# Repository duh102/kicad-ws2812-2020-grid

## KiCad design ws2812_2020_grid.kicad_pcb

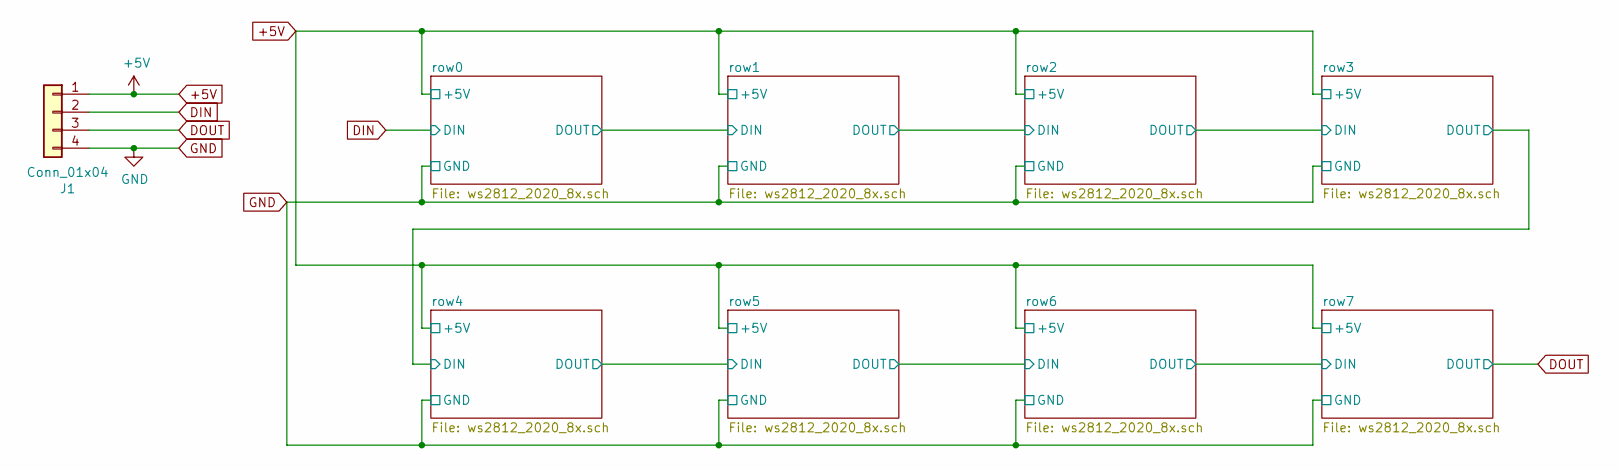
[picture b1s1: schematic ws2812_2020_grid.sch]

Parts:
J1: Conn_01x04; PinHeader_1x04_P2.54mm_Vertical

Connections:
+5V: J1.1; also elsewhere on the board
DIN: J1.2; also elsewhere on the board
DOUT: J1.3; also elsewhere on the board
GND: J1.4; also elsewhere on the board

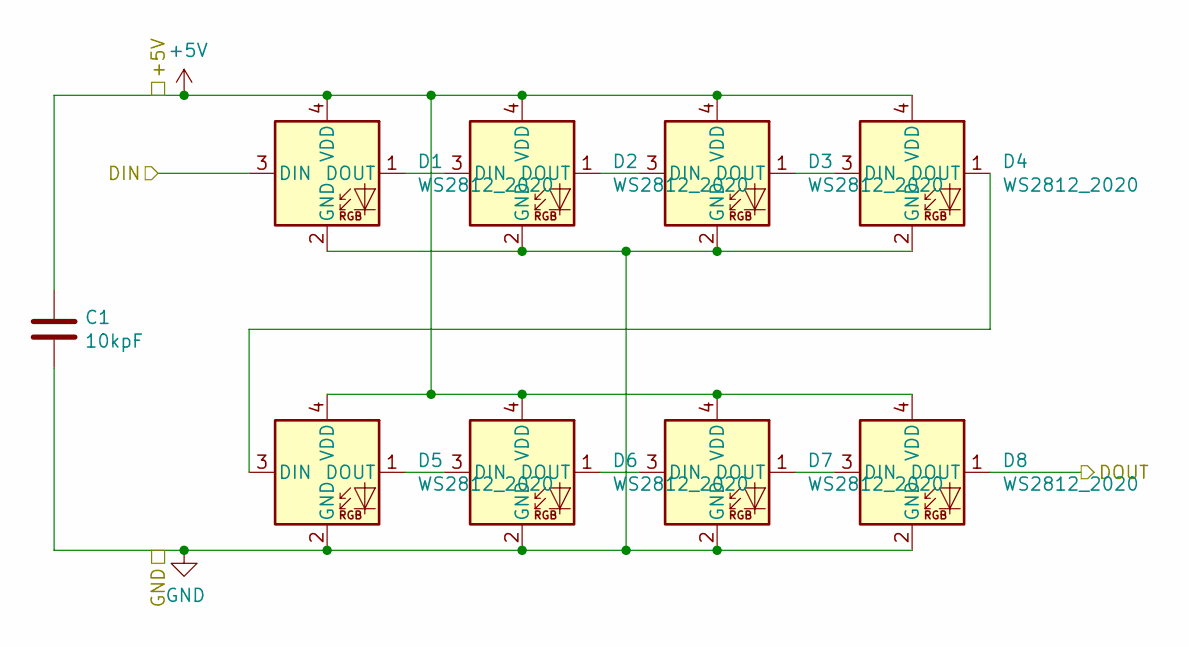
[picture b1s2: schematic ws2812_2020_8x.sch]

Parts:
C1: 10kpF; C_0805_2012Metric
D1, D2, D3, D4, D5, D6, D7, D8: WS2812_2020; LED_WS2812_2020_2.0x2.0mm

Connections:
+5V: C1.1, D1.4 (VDD), D2.4 (VDD), D3.4 (VDD), D4.4 (VDD), D5.4 (VDD), D6.4 (VDD), D7.4 (VDD), D8.4 (VDD); also elsewhere on the board
/row1/DIN: D8.1 (DOUT); also elsewhere on the board
DIN: D1.3 (DIN); also elsewhere on the board
GND: C1.2, D1.2 (GND), D2.2 (GND), D3.2 (GND), D4.2 (GND), D5.2 (GND), D6.2 (GND), D7.2 (GND), D8.2 (GND); also elsewhere on the board
unnamed: D1.1 (DOUT), D2.3 (DIN)
unnamed: D2.1 (DOUT), D3.3 (DIN)
unnamed: D3.1 (DOUT), D4.3 (DIN)
unnamed: D4.1 (DOUT), D5.3 (DIN)
unnamed: D5.1 (DOUT), D6.3 (DIN)
unnamed: D6.1 (DOUT), D7.3 (DIN)
unnamed: D7.1 (DOUT), D8.3 (DIN)

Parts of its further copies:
C2, C3, C4, C5, C6, C7, C8: 10kpF; C_0805_2012Metric
D9, D10, D11, D12, D13, D14, D15, D16, D17, D18, D19, D20, D21, D22, D23, D24, D25, D26, D27, D28, D29, D30, D31, D32, D33, D34, D35, D36, D37, D38, D39, D40, D41, D42, D43, D44, D45, D46, D47, D48, D49, D50, D51, D52, D53, D54, D55, D56, D57, D58, D59, D60, D61, D62, D63, D64: WS2812_2020; LED_WS2812_2020_2.0x2.0mm

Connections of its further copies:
+5V: C2.1, C3.1, C4.1, C5.1, C6.1, C7.1, C8.1, D9.4 (VDD), D10.4 (VDD), D11.4 (VDD), D12.4 (VDD), D13.4 (VDD), D14.4 (VDD), D15.4 (VDD), D16.4 (VDD), D17.4 (VDD), D18.4 (VDD), D19.4 (VDD), D20.4 (VDD), D21.4 (VDD), D22.4 (VDD), D23.4 (VDD), D24.4 (VDD), D25.4 (VDD), D26.4 (VDD), D27.4 (VDD), D28.4 (VDD), D29.4 (VDD), D30.4 (VDD), D31.4 (VDD), D32.4 (VDD), D33.4 (VDD), D34.4 (VDD), D35.4 (VDD), D36.4 (VDD), D37.4 (VDD), D38.4 (VDD), D39.4 (VDD), D40.4 (VDD), D41.4 (VDD), D42.4 (VDD), D43.4 (VDD), D44.4 (VDD), D45.4 (VDD), D46.4 (VDD), D47.4 (VDD), D48.4 (VDD), D49.4 (VDD), D50.4 (VDD), D51.4 (VDD), D52.4 (VDD), D53.4 (VDD), D54.4 (VDD), D55.4 (VDD), D56.4 (VDD), D57.4 (VDD), D58.4 (VDD), D59.4 (VDD), D60.4 (VDD), D61.4 (VDD), D62.4 (VDD), D63.4 (VDD), D64.4 (VDD); also elsewhere on the board
/row1/DIN: D9.3 (DIN); also elsewhere on the board
/row2/DIN: D16.1 (DOUT), D17.3 (DIN)
/row3/DIN: D24.1 (DOUT), D25.3 (DIN)
/row4/DIN: D32.1 (DOUT), D33.3 (DIN)
/row5/DIN: D40.1 (DOUT), D41.3 (DIN)
/row6/DIN: D48.1 (DOUT), D49.3 (DIN)
/row7/DIN: D56.1 (DOUT), D57.3 (DIN)
DOUT: D64.1 (DOUT); also elsewhere on the board
GND: C2.2, C3.2, C4.2, C5.2, C6.2, C7.2, C8.2, D9.2 (GND), D10.2 (GND), D11.2 (GND), D12.2 (GND), D13.2 (GND), D14.2 (GND), D15.2 (GND), D16.2 (GND), D17.2 (GND), D18.2 (GND), D19.2 (GND), D20.2 (GND), D21.2 (GND), D22.2 (GND), D23.2 (GND), D24.2 (GND), D25.2 (GND), D26.2 (GND), D27.2 (GND), D28.2 (GND), D29.2 (GND), D30.2 (GND), D31.2 (GND), D32.2 (GND), D33.2 (GND), D34.2 (GND), D35.2 (GND), D36.2 (GND), D37.2 (GND), D38.2 (GND), D39.2 (GND), D40.2 (GND), D41.2 (GND), D42.2 (GND), D43.2 (GND), D44.2 (GND), D45.2 (GND), D46.2 (GND), D47.2 (GND), D48.2 (GND), D49.2 (GND), D50.2 (GND), D51.2 (GND), D52.2 (GND), D53.2 (GND), D54.2 (GND), D55.2 (GND), D56.2 (GND), D57.2 (GND), D58.2 (GND), D59.2 (GND), D60.2 (GND), D61.2 (GND), D62.2 (GND), D63.2 (GND), D64.2 (GND); also elsewhere on the board
unnamed: D10.1 (DOUT), D11.3 (DIN)
unnamed: D9.1 (DOUT), D10.3 (DIN)
unnamed: D11.1 (DOUT), D12.3 (DIN)
unnamed: D12.1 (DOUT), D13.3 (DIN)
unnamed: D13.1 (DOUT), D14.3 (DIN)
unnamed: D14.1 (DOUT), D15.3 (DIN)
unnamed: D15.1 (DOUT), D16.3 (DIN)
unnamed: D17.1 (DOUT), D18.3 (DIN)
unnamed: D18.1 (DOUT), D19.3 (DIN)
unnamed: D19.1 (DOUT), D20.3 (DIN)
unnamed: D20.1 (DOUT), D21.3 (DIN)
unnamed: D21.1 (DOUT), D22.3 (DIN)
unnamed: D22.1 (DOUT), D23.3 (DIN)
unnamed: D23.1 (DOUT), D24.3 (DIN)
unnamed: D25.1 (DOUT), D26.3 (DIN)
unnamed: D26.1 (DOUT), D27.3 (DIN)
unnamed: D27.1 (DOUT), D28.3 (DIN)
unnamed: D28.1 (DOUT), D29.3 (DIN)
unnamed: D29.1 (DOUT), D30.3 (DIN)
unnamed: D30.1 (DOUT), D31.3 (DIN)
unnamed: D31.1 (DOUT), D32.3 (DIN)
unnamed: D33.1 (DOUT), D34.3 (DIN)
unnamed: D34.1 (DOUT), D35.3 (DIN)
unnamed: D35.1 (DOUT), D36.3 (DIN)
unnamed: D36.1 (DOUT), D37.3 (DIN)
unnamed: D37.1 (DOUT), D38.3 (DIN)
unnamed: D38.1 (DOUT), D39.3 (DIN)
unnamed: D39.1 (DOUT), D40.3 (DIN)
unnamed: D41.1 (DOUT), D42.3 (DIN)
unnamed: D42.1 (DOUT), D43.3 (DIN)
unnamed: D43.1 (DOUT), D44.3 (DIN)
unnamed: D44.1 (DOUT), D45.3 (DIN)
unnamed: D45.1 (DOUT), D46.3 (DIN)
unnamed: D46.1 (DOUT), D47.3 (DIN)
unnamed: D47.1 (DOUT), D48.3 (DIN)
unnamed: D49.1 (DOUT), D50.3 (DIN)
unnamed: D50.1 (DOUT), D51.3 (DIN)
unnamed: D51.1 (DOUT), D52.3 (DIN)
unnamed: D52.1 (DOUT), D53.3 (DIN)
unnamed: D53.1 (DOUT), D54.3 (DIN)
unnamed: D54.1 (DOUT), D55.3 (DIN)
unnamed: D55.1 (DOUT), D56.3 (DIN)
unnamed: D57.1 (DOUT), D58.3 (DIN)
unnamed: D58.1 (DOUT), D59.3 (DIN)
unnamed: D59.1 (DOUT), D60.3 (DIN)
unnamed: D60.1 (DOUT), D61.3 (DIN)
unnamed: D61.1 (DOUT), D62.3 (DIN)
unnamed: D62.1 (DOUT), D63.3 (DIN)
unnamed: D63.1 (DOUT), D64.3 (DIN)

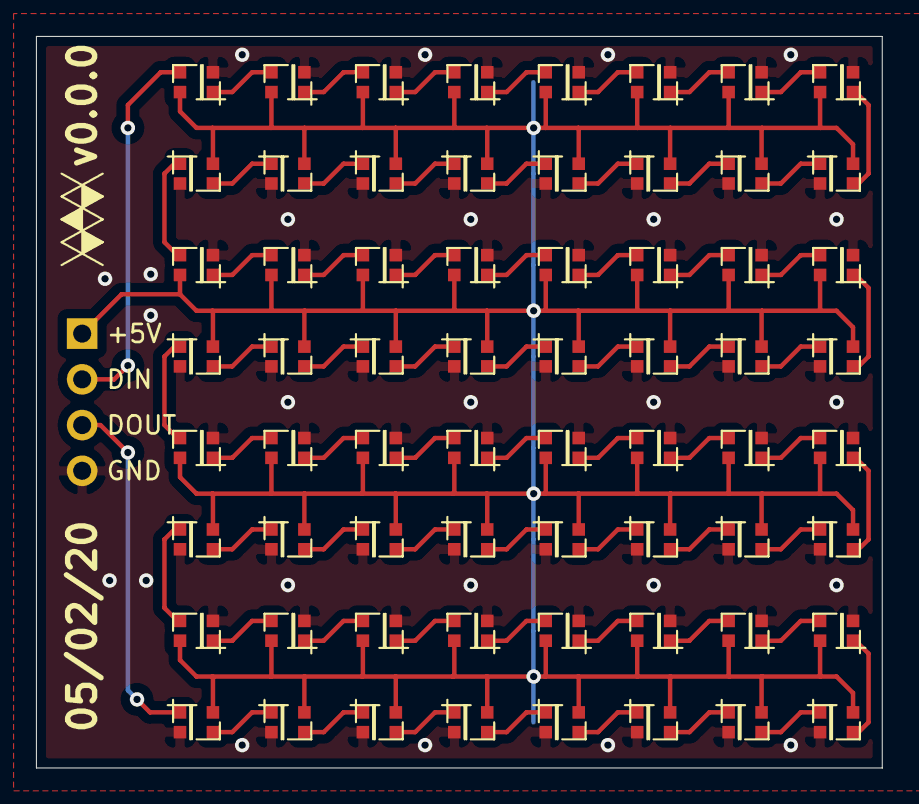
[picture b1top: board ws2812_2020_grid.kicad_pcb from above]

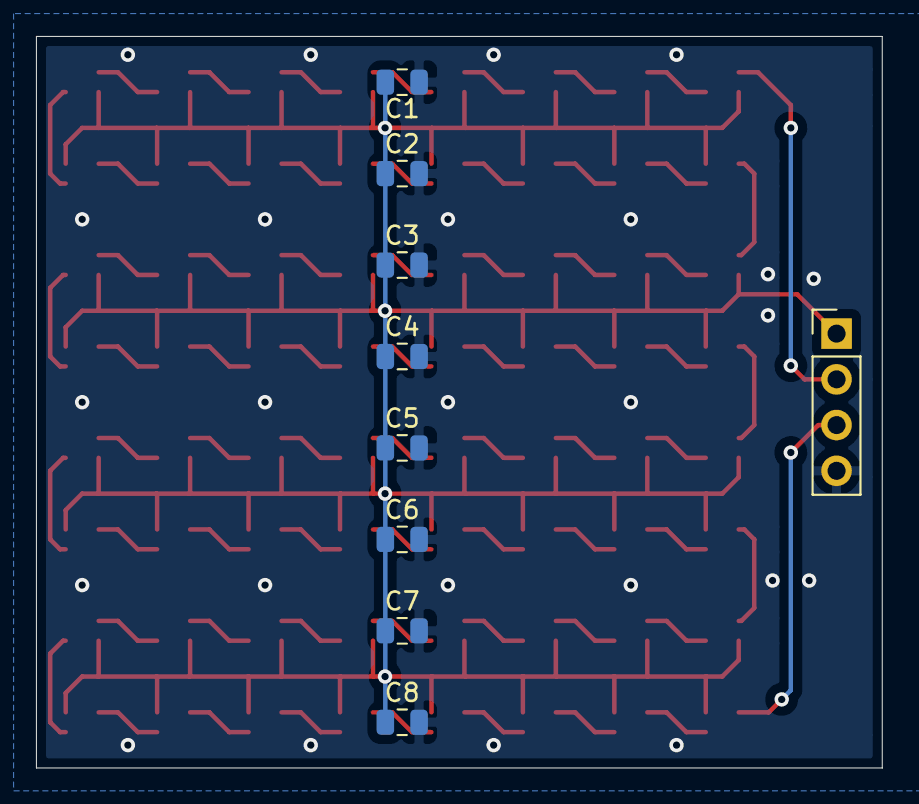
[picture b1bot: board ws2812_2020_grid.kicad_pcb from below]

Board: 2 copper layers, 47.0 x 40.6 mm, 73 parts (9 on the bottom side), 67 nets.

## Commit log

2020-12-09 Minor updates
